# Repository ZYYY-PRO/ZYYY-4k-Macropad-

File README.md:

# ZYYYPAD
All the files that are required to produce the pcb is opensource

<b> https://youtu.be/lbP1HDdJELI video BTW

---

Visit here for the Billing of Material: **Parts.md**

---

Project Log: ZYYY 4k-Macropad

| Mentor: Mr. Porczek
Official Timeline: Sept 2025 – Jan 23, 2026

---
# I. The Research & Design Phase
## SEPTEMBER 2025 - Research & Logic

    Started deep-dive research into mechanical keyboard mounting styles (Gasket vs. Tray).

    Analyzed the RP2040 Datasheet to understand pin mapping.

    Studied the Keyboard Matrix logic to plan the 4x5 layout.

## OCTOBER 2025 - Electrical Engineering

    Began schematic design in KiCad.

    Integrated the MCU, USB-C components, and the Rotary Encoder into the circuit.

    Finalized the diode-per-switch logic to ensure NKRO (N-Key Rollover).

## NOVEMBER 2025 - PCB Layout & Routing

    Spent the month physically routing traces on the PCB.

    Designed the "ZYYY 4KPAD" aesthetic silkscreen for the back of the board.

## DECEMBER 2025 - 3D Mechanical Modeling

    Began 3D modeling the enclosure in Autodesk Fusion.

    Designed custom "scooped" ergonomic keycaps and the encoder knob.
---
# II. The Crisis & Pivot
## JANUARY 8, 2026 - The SSD Disaster

    22:58 PM: Catastrophic hardware failure. The laptop fell and broke; the internal SSD fried.

    Result: Loss of all original KiCad files, Fusion models, and raw video footage.

## JANUARY 9, 2026 - Emergency Mentorship

    Met with Mr. Porczek to assess the damage.

    He helped boost confidence and helped plan the "Challenging 2-Week Completion" recovery phase.

    Switched all project files to a dedicated External SSD for safety.

## JANUARY 12 - 15, 2026 - Rapid Re-Design

    Redid the entire KiCad schematic and PCB layout from memory.

    Attempted to order parts from JLCPCB; discovered RP2040 and Component Shortfalls.

    Decision: Pivoted to a full 3D-printed functional prototype to meet the school deadline.
---
# III. Production & Final Sprint
## JANUARY 16, 2026 - Fusion Redux

    Remodelled the entire case and keycap set in Fusion to optimize for 3D printing.

## JANUARY 17, 2026 - Start of Manufacturing

    Started mass-printing parts on the Bambu Lab P2S.

    Began the Video Editing Phase in DaVinci Resolve, reconstructing the narrative of the project.

## JANUARY 18, 2026 - 3D Printing & Recording

    Printed the bottom frame and 20 individual keycaps.

    Recorded "B-Roll" footage of the printing process using the Insta360 Ace Pro 2.

## JANUARY 19, 2026 - Assembly & Demo Recording

    Final physical assembly: Fitting switches and keycaps into the frames.

    Recorded functional tests, including the volume knob and video editing macros.

## JANUARY 20 - 21, 2026 - Non-Stop Video Editing

    16-hour sessions in DaVinci Resolve.

    Synced the "Friday Night Funkin" gameplay footage to demonstrate the device's use cases.

    Voice-over for videos.

## JANUARY 22, 2026 - Final Polish & Canva Prep

    Added meme-overlays, 2017-style music transitions, and final project credits.

    Compiled all files, source code, and images into the final Canva Presentation.

## JANUARY 23, 2026 - Final Presentation & Upload

    Morning: Presented the 4K-Macropad live in class. Demonstrated the rotary encoder and editing shortcuts.

    Afternoon: Final video upload and GitHub repository push.
---
#  Project officially marked as SEMI-COMPLETED.
# Stay tune for part 2

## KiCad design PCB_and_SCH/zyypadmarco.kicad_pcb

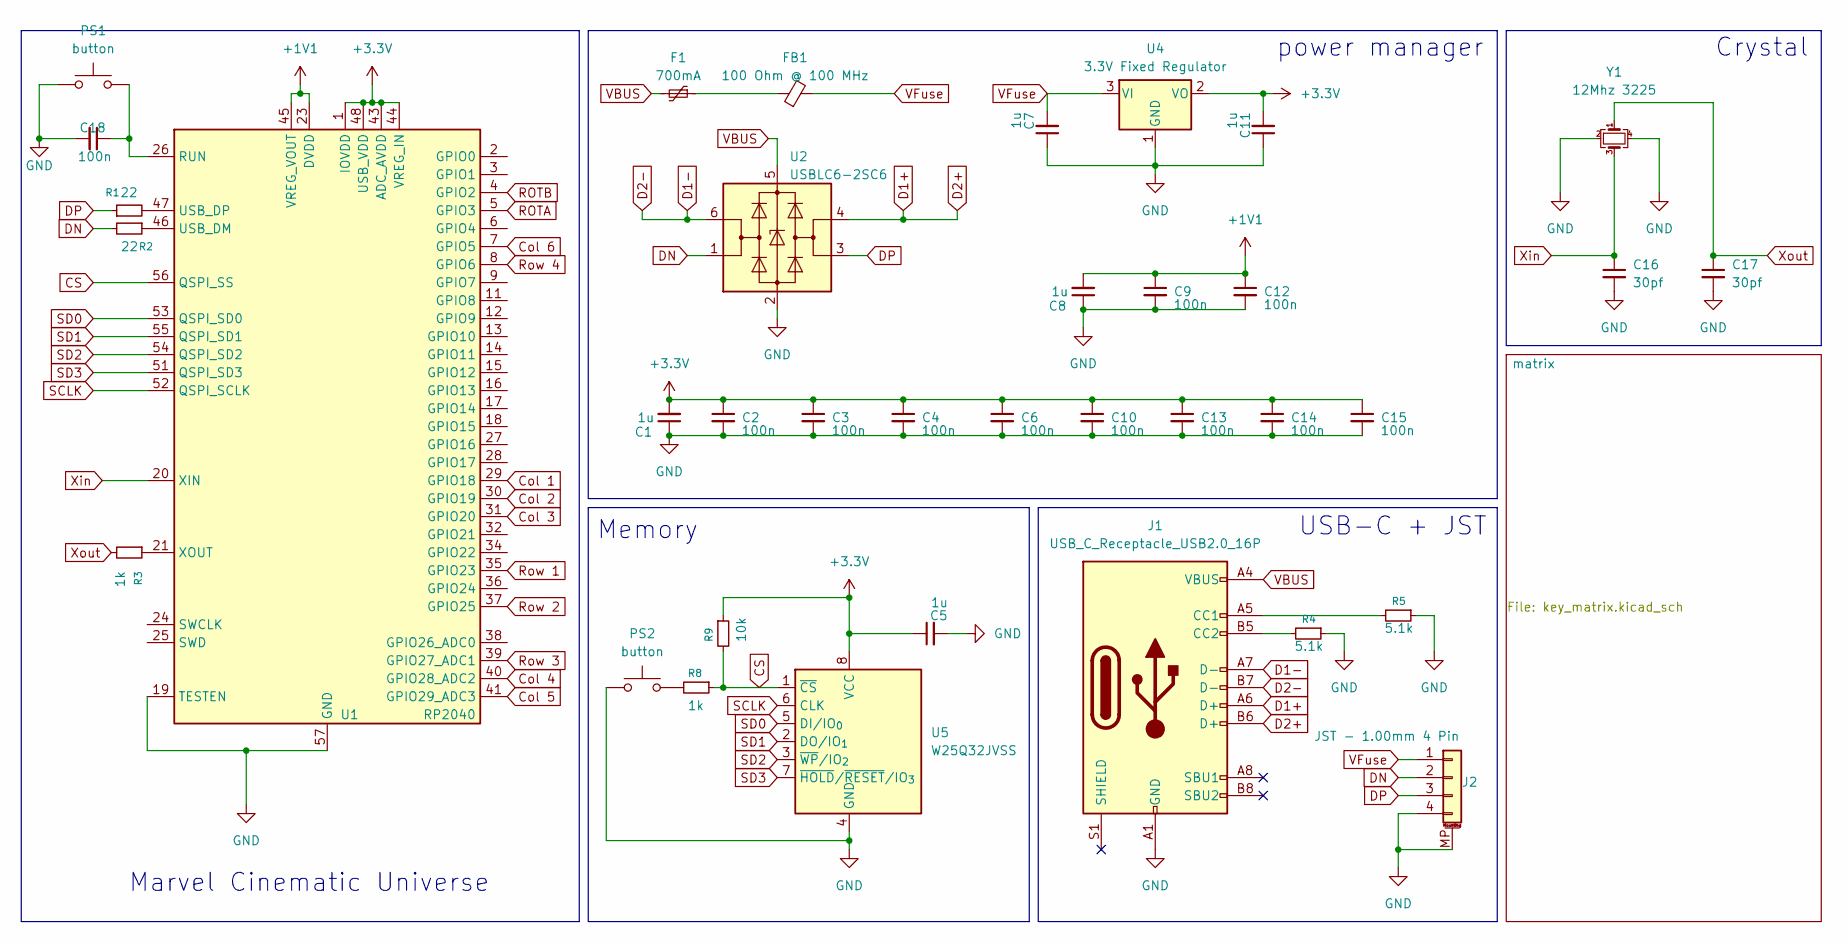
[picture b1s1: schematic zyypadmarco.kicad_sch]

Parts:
C1, C5, C7, C8, C11: 1u; C_0402_1005Metric; LCSC C52923
C2, C3, C4, C6, C9, C10, C12, C13, C14, C15, C18: 100n; C_0402_1005Metric; LCSC C1525
C16, C17: 30pf; C_0402_1005Metric
F1: 700mA; Fuse_0402_1005Metric; LCSC C914086
FB1: 100 Ohm @ 100 MHz; L_0402_1005Metric; LCSC C85812
J1: USB_C_Receptacle_USB2.0_16P; USB_C_Receptacle_GCT_USB4105-xx-A_16P_TopMnt_Horizontal
J2: JST - 1.00mm 4 Pin; JST_SH_SM04B-SRSS-TB_1x04-1MP_P1.00mm_Horizontal; LCSC C160404
PS1, PS2: button; SW_Push_1P1T_NO_E-Switch_TL3301NxxxxxG
R1, R2: 22; R_0402_1005Metric
R3, R8: 1k; R_0402_1005Metric
R4, R5: 5.1k; R_0402_1005Metric
R9: 10k; R_0402_1005Metric
U1: RP2040; QFN-56-1EP_7x7mm_P0.4mm_EP3.2x3.2mm
U2: USBLC6-2SC6; SOT-23-6; LCSC C558442
U4: 3.3V Fixed Regulator; TSOT-23; LCSC C150715
U5: W25Q32JVSS; SOIC-8_5.3x5.3mm_P1.27mm
Y1: 12Mhz 3225; Crystal_SMD_3225-4Pin_3.2x2.5mm_HandSoldering

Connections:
+1V1: C8.2, C9.1, C12.1, U1.23 (DVDD), U1.45 (VREG_VOUT), U1.50 (DVDD)
+3.3V: C1.2, C2.1, C3.1, C4.1, C5.1, C6.1, C10.1, C11.2, C13.1, C14.1, C15.1, R9.1, U1.1 (IOVDD), U1.10 (IOVDD), U1.22 (IOVDD), U1.33 (IOVDD), U1.42 (IOVDD), U1.43 (ADC_AVDD), U1.44 (VREG_IN), U1.48 (USB_VDD), U1.49 (IOVDD), U4.2 (VO), U5.8 (VCC); also elsewhere on the board
CS: R8.1, R9.2, U1.56 (QSPI_SS), U5.1 (~CS)
Col 1: U1.29 (GPIO18); also elsewhere on the board
Col 2: U1.30 (GPIO19); also elsewhere on the board
Col 3: U1.31 (GPIO20); also elsewhere on the board
Col 4: U1.40 (GPIO28_ADC2); also elsewhere on the board
Col 5: U1.41 (GPIO29_ADC3); also elsewhere on the board
Col 6: U1.7 (GPIO5); also elsewhere on the board
D1+: J1.A6 (D+), J1.B6 (D+), U2.4 (I/O2)
D1-: J1.A7 (D-), J1.B7 (D-), U2.6 (I/O1)
DN: J2.2, R2.2, U2.1 (I/O1)
DP: J2.3, R1.1, U2.3 (I/O2)
GND: C1.1, C2.2, C3.2, C4.2, C5.2, C6.2, C7.1, C8.1, C9.2, C10.2, C11.1, C12.2, C13.2, C14.2, C15.2, C16.2, C17.2, C18.2, J1.A1 (GND), J1.A12 (GND), J1.B1 (GND), J1.B12 (GND), J2.4, J2.MP (MountPin), PS1.1, PS2.1, R4.1, R5.1, U1.19 (TESTEN), U1.57 (GND), U2.2 (GND), U4.1 (GND), U5.4 (GND), Y1.2, Y1.4; also elsewhere on the board
unnamed: F1.1, FB1.1
unnamed: J1.A5 (CC1), R5.2
unnamed: J1.B5 (CC2), R4.2
unnamed: PS2.2, R8.2
unnamed: C18.1, PS1.2, U1.26 (RUN)
unnamed: R2.1, U1.46 (USB_DM)
unnamed: R1.2, U1.47 (USB_DP)
unnamed: R3.1, U1.21 (XOUT)
ROTA: U1.5 (GPIO3); also elsewhere on the board
ROTB: U1.4 (GPIO2); also elsewhere on the board
Row 1: U1.35 (GPIO23); also elsewhere on the board
Row 2: U1.37 (GPIO25); also elsewhere on the board
Row 3: U1.39 (GPIO27_ADC1); also elsewhere on the board
Row 4: U1.8 (GPIO6); also elsewhere on the board
SCLK: U1.52 (QSPI_SCLK), U5.6 (CLK)
SD0: U1.53 (QSPI_SD0), U5.5 (DI/IO_{0})
SD1: U1.55 (QSPI_SD1), U5.2 (DO/IO_{1})
SD2: U1.54 (QSPI_SD2), U5.3 (~WP/IO_{2})
SD3: U1.51 (QSPI_SD3), U5.7 (~HOLD/~RESET/IO_{3})
VBUS: F1.2, J1.A4 (VBUS), J1.A9 (VBUS), J1.B4 (VBUS), J1.B9 (VBUS), U2.5 (VBUS)
VFuse: C7.2, FB1.2, J2.1, U4.3 (VI)
Xin: C16.1, U1.20 (XIN), Y1.3
Xout: C17.1, R3.2, Y1.1

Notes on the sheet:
Memory
Marvel Cinematic Universe
power manager
USB-C + JST
Crystal

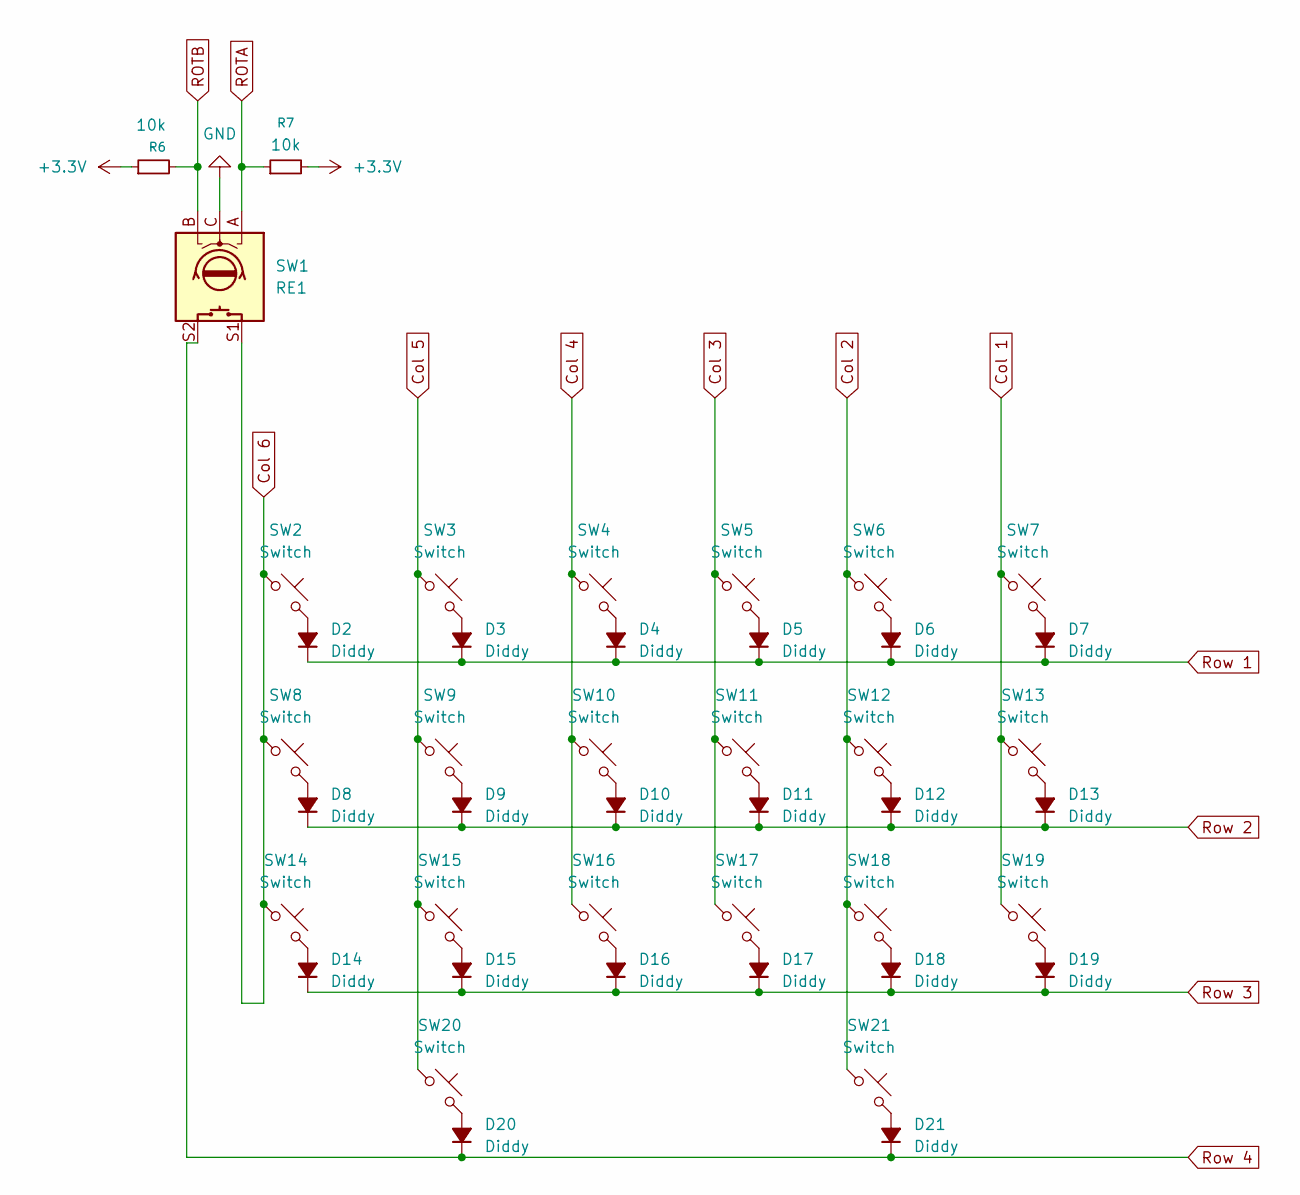
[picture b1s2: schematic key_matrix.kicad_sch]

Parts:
D2, D3, D4, D5, D6, D7, D8, D9, D10, D11, D12, D13, D14, D15, D16, D17, D18, D19, D20, D21: Diddy; D_SOD-123
R6, R7: 10k; R_0402_1005Metric
SW1: RE1; ROT_Alps_EC11E-Switch
SW2, SW3, SW4, SW5, SW6, SW7, SW8, SW9, SW10, SW11, SW12, SW13, SW14, SW15, SW16, SW17, SW18, SW19, SW20, SW21: Switch; SW_MX_HS_CPG151101S11_1u

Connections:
+3.3V: R6.1, R7.2; also elsewhere on the board
Col 1: SW7.1, SW13.1, SW19.1; also elsewhere on the board
Col 2: SW6.1, SW12.1, SW18.1, SW21.1; also elsewhere on the board
Col 3: SW5.1, SW11.1, SW17.1; also elsewhere on the board
Col 4: SW4.1, SW10.1, SW16.1; also elsewhere on the board
Col 5: SW3.1, SW9.1, SW15.1, SW20.1; also elsewhere on the board
Col 6: SW1.S1, SW2.1, SW8.1, SW14.1; also elsewhere on the board
GND: SW1.C; also elsewhere on the board
unnamed: D2.2 (A), SW2.2
unnamed: D3.2 (A), SW3.2
unnamed: D4.2 (A), SW4.2
unnamed: D5.2 (A), SW5.2
unnamed: D6.2 (A), SW6.2
unnamed: D7.2 (A), SW7.2
unnamed: D8.2 (A), SW8.2
unnamed: D9.2 (A), SW9.2
unnamed: D10.2 (A), SW10.2
unnamed: D11.2 (A), SW11.2
unnamed: D12.2 (A), SW12.2
unnamed: D13.2 (A), SW13.2
unnamed: D14.2 (A), SW14.2
unnamed: D15.2 (A), SW15.2
unnamed: D16.2 (A), SW16.2
unnamed: D17.2 (A), SW17.2
unnamed: D18.2 (A), SW18.2
unnamed: D19.2 (A), SW19.2
unnamed: D20.2 (A), SW20.2
unnamed: D21.2 (A), SW21.2
ROTA: R7.1, SW1.A; also elsewhere on the board
ROTB: R6.2, SW1.B; also elsewhere on the board
Row 1: D2.1 (K), D3.1 (K), D4.1 (K), D5.1 (K), D6.1 (K), D7.1 (K); also elsewhere on the board
Row 2: D8.1 (K), D9.1 (K), D10.1 (K), D11.1 (K), D12.1 (K), D13.1 (K); also elsewhere on the board
Row 3: D14.1 (K), D15.1 (K), D16.1 (K), D17.1 (K), D18.1 (K), D19.1 (K); also elsewhere on the board
Row 4: D20.1 (K), D21.1 (K), SW1.S2; also elsewhere on the board

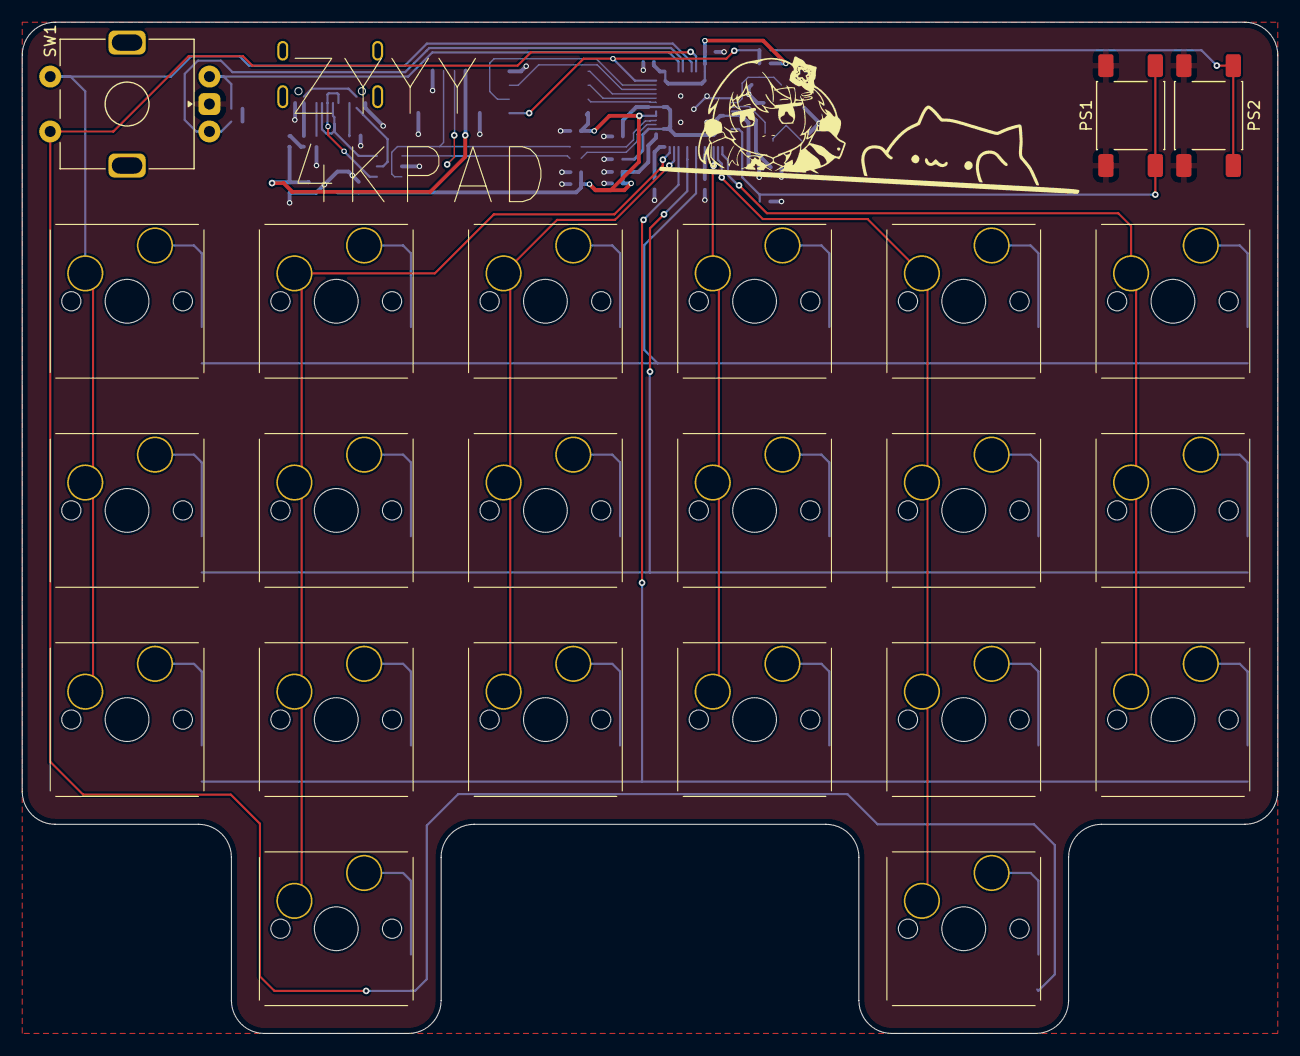
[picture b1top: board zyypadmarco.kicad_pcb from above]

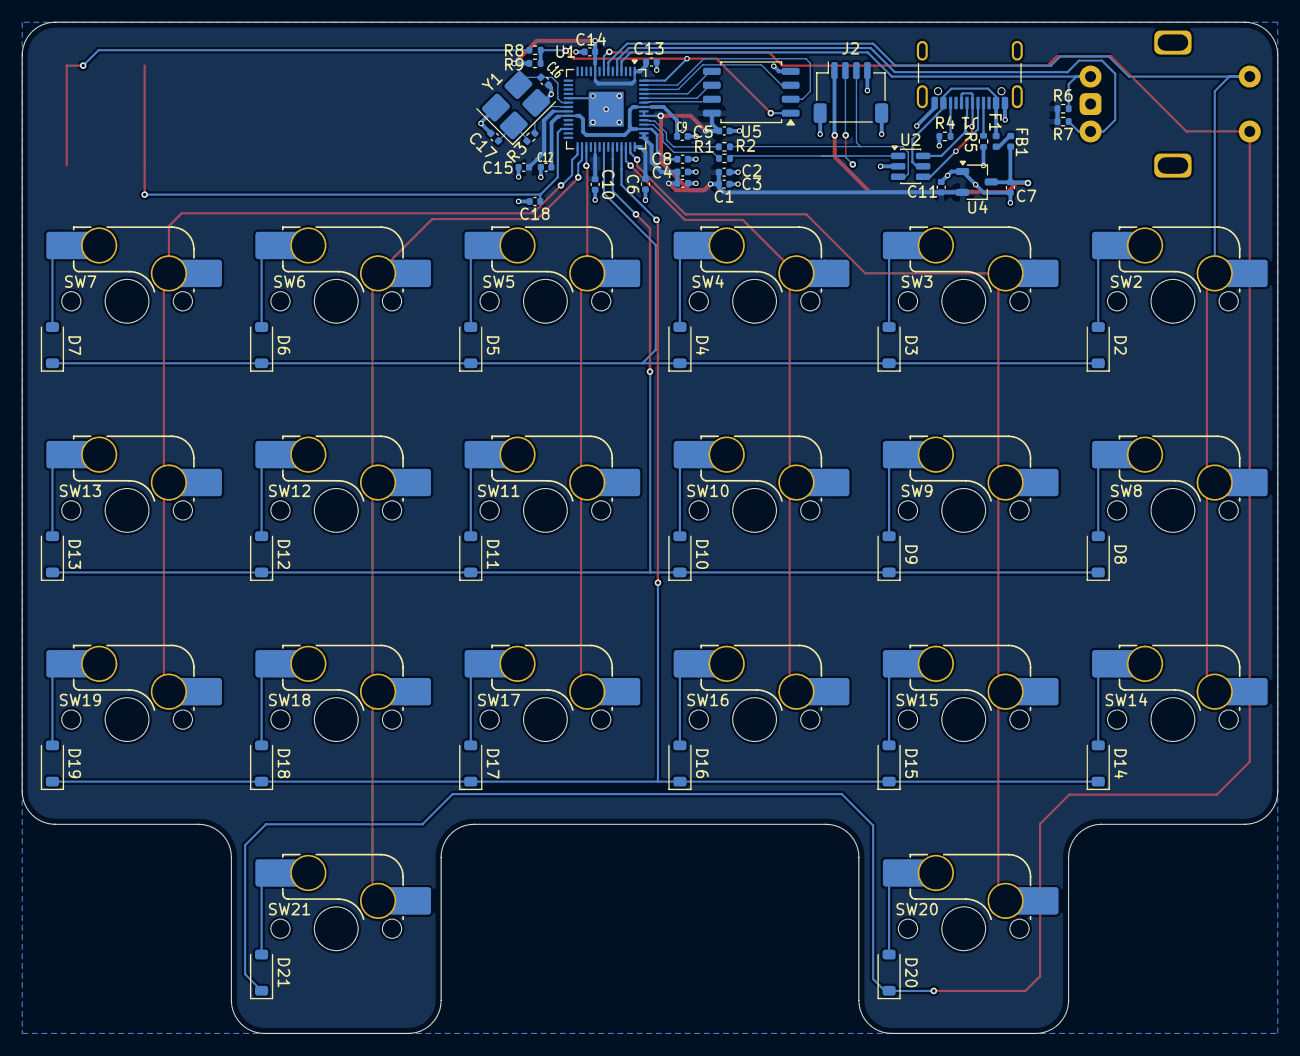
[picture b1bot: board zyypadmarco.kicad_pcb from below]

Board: 2 copper layers, 114.4 x 92.1 mm, 79 parts (76 on the bottom side), 57 nets.

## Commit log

2026-01-25 project log and timeline
    Expanded project log with detailed phases from research to final presentation.
2026-01-25 Refine section headers and improve formatting
    Updated section headers for consistency and clarity, correcting formatting and phrasing throughout the timeline.
2026-01-25 Change project status to SEMI-COMPLETED
    Updated project status from COMPLETED to SEMI-COMPLETED and added a note for part 2.
2026-01-25 Fix typo in README section header
2026-03-28 Parts.md
2026-03-28 Update Parts.md with additional component images
    Added images and details for top components and switches needed for PCB soldering.
2026-03-28 gerber and stuff
